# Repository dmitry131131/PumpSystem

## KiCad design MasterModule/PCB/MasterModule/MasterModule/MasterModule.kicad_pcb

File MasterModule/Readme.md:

# MasterModule

Мастер-модуль на STM32F103 для управления модулями насосов по CAN.

- [Code](Code/Readme.md) — прошивка, конфигурация платы, сборка и прошивка через ST-Link.
- `PCB/` — проект печатной платы.
- `3DModel/` — механические модели.

Сборка из каталога `MasterModule`:

```bash
cd Code
cmake --preset Debug
cmake --build --preset Debug
```

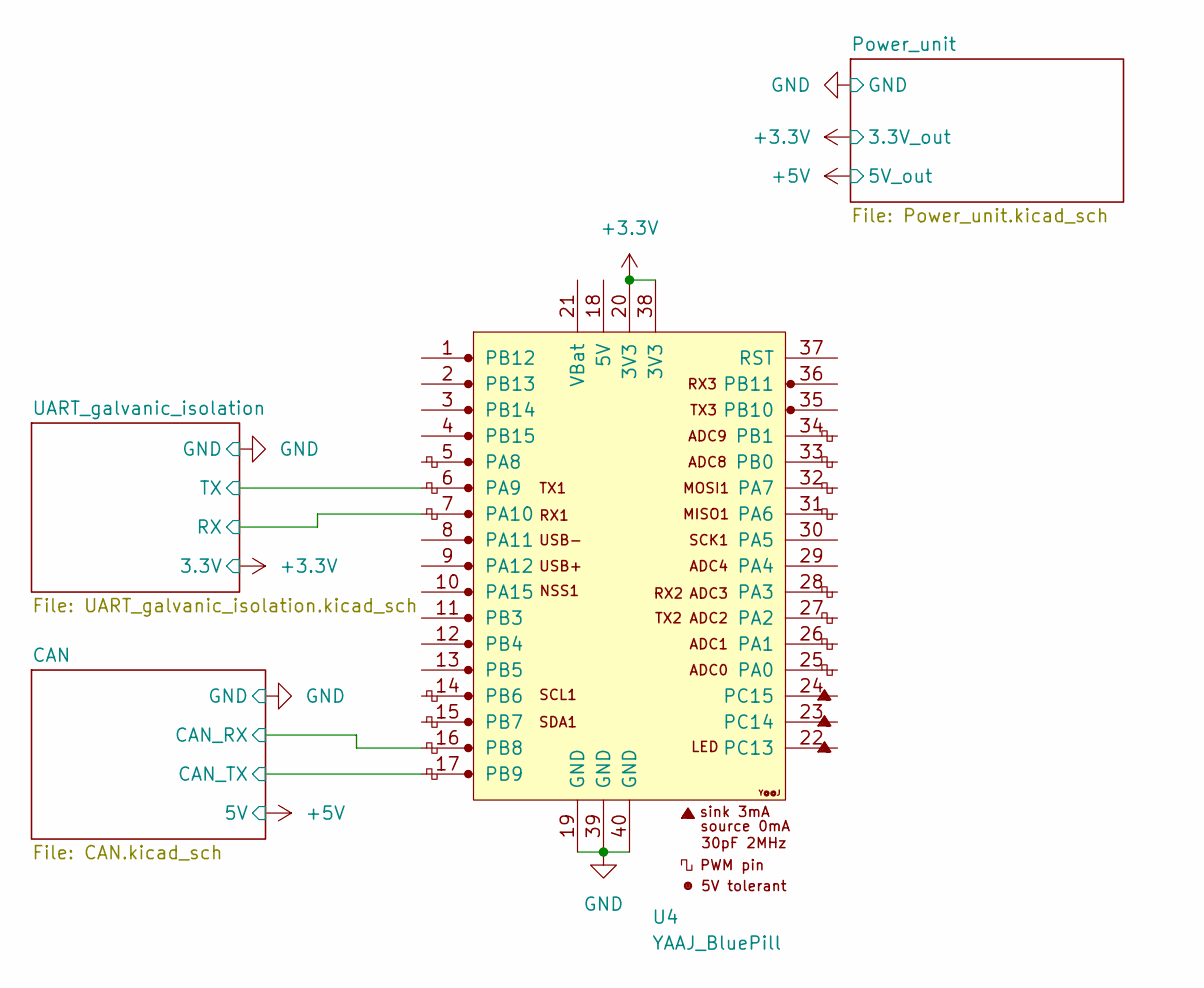
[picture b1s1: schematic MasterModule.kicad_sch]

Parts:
U4: YAAJ_BluePill; YAAJ_BluePill_1

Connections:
+3.3V: U4.20 (3V3), U4.38 (3V3); also elsewhere on the board
/CAN/CAN_RX: U4.16 (PB8); also elsewhere on the board
/CAN/CAN_TX: U4.17 (PB9); also elsewhere on the board
/UART_galvanic_isolation/RX: U4.7 (PA10); also elsewhere on the board
/UART_galvanic_isolation/TX: U4.6 (PA9); also elsewhere on the board
GND: U4.19 (GND), U4.39 (GND), U4.40 (GND); also elsewhere on the board

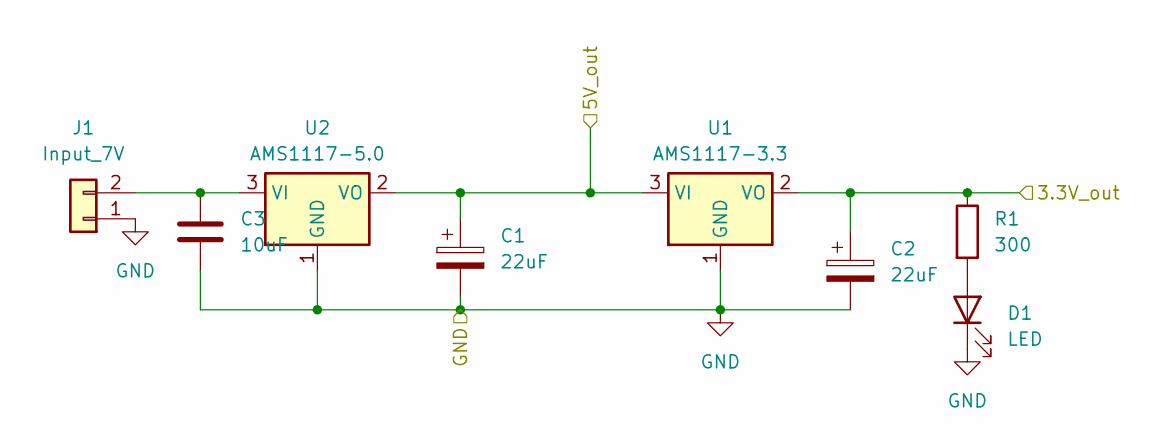
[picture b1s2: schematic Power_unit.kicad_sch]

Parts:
C1, C2: 22uF; C_1210_3225Metric_Pad1.33x2.70mm_HandSolder
C3: 10uF; C_0603_1608Metric_Pad1.08x0.95mm_HandSolder
D1: LED; LED_0805_2012Metric_Pad1.15x1.40mm_HandSolder
J1: Input_7V; TerminalBlock_Phoenix_MKDS-1,5-2-5.08_1x02_P5.08mm_Horizont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
R1: 300; R_0805_2012Metric_Pad1.20x1.40mm_HandSolder
U1: AMS1117-3.3; SOT-223-3_TabPin2
U2: AMS1117-5.0; SOT-223-3_TabPin2

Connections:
+3.3V: C2.1, R1.1, U1.2 (VO); also elsewhere on the board
+5V: C1.1, U1.3 (VI), U2.2 (VO); also elsewhere on the board
GND: C1.2, C2.2, C3.2, D1.1 (K), J1.1, U1.1 (GND), U2.1 (GND); also elsewhere on the board
unnamed: D1.2 (A), R1.2
unnamed: C3.1, J1.2, U2.3 (VI)

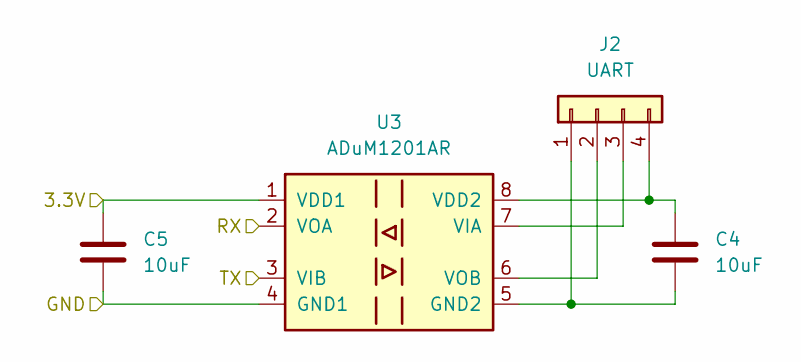
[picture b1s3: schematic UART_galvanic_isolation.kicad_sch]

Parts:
C4, C5: 10uF; C_0805_2012Metric_Pad1.18x1.45mm_HandSolder
J2: UART; JST_XH_B4B-XH-A_1x04_P2.50mm_Vertical
U3: ADuM1201AR; SOIC-8_3.9x4.9mm_P1.27mm

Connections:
+3.3V: C5.1, U3.1 (VDD1); also elsewhere on the board
/UART_galvanic_isolation/RX: U3.2 (VOA); also elsewhere on the board
/UART_galvanic_isolation/TX: U3.3 (VIB); also elsewhere on the board
GND: C5.2, U3.4 (GND1); also elsewhere on the board
unnamed: C4.2, J2.1, U3.5 (GND2)
unnamed: J2.2, U3.6 (VOB)
unnamed: J2.3, U3.7 (VIA)
unnamed: C4.1, J2.4, U3.8 (VDD2)

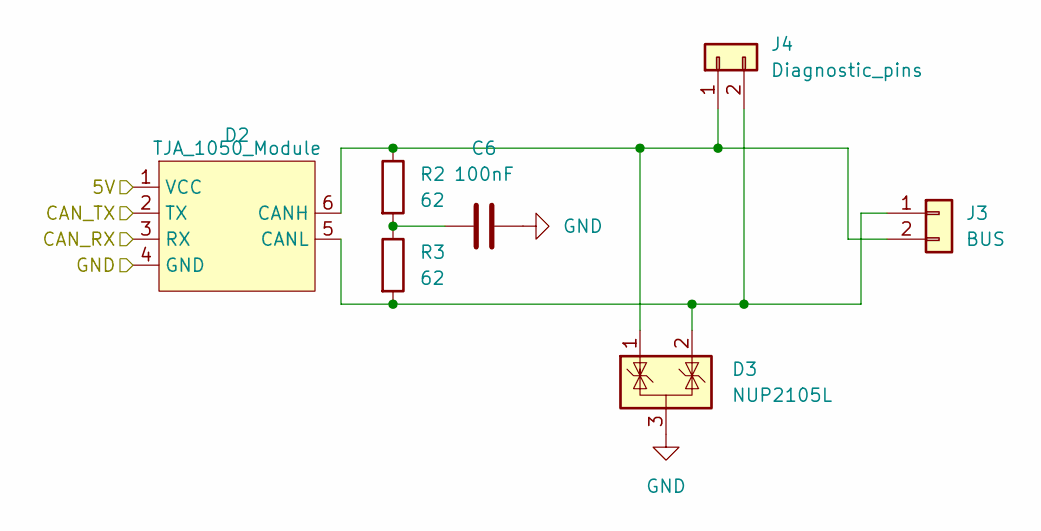
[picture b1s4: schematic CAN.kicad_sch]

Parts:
C6: 100nF; C_0805_2012Metric_Pad1.18x1.45mm_HandSolder
D2: TJA_1050_Module; TJA1050_module
D3: NUP2105L; SOT-23
J3: BUS; JST_XH_B2B-XH-A_1x02_P2.50mm_Vertical
J4: Diagnostic_pins; PinSocket_1x02_P2.54mm_Vertical
R2, R3: 62; R_0805_2012Metric_Pad1.20x1.40mm_HandSolder

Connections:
GND: C6.2, D3.3 (A); also elsewhere on the board
unnamed: C6.1, R2.2, R3.1
unnamed 14: D2.5 (CANL), D3.2 (K), J3.1, J4.2, R3.2; also elsewhere on the board
unnamed 15: D2.6 (CANH), D3.1 (K), J3.2, J4.1, R2.1; also elsewhere on the board

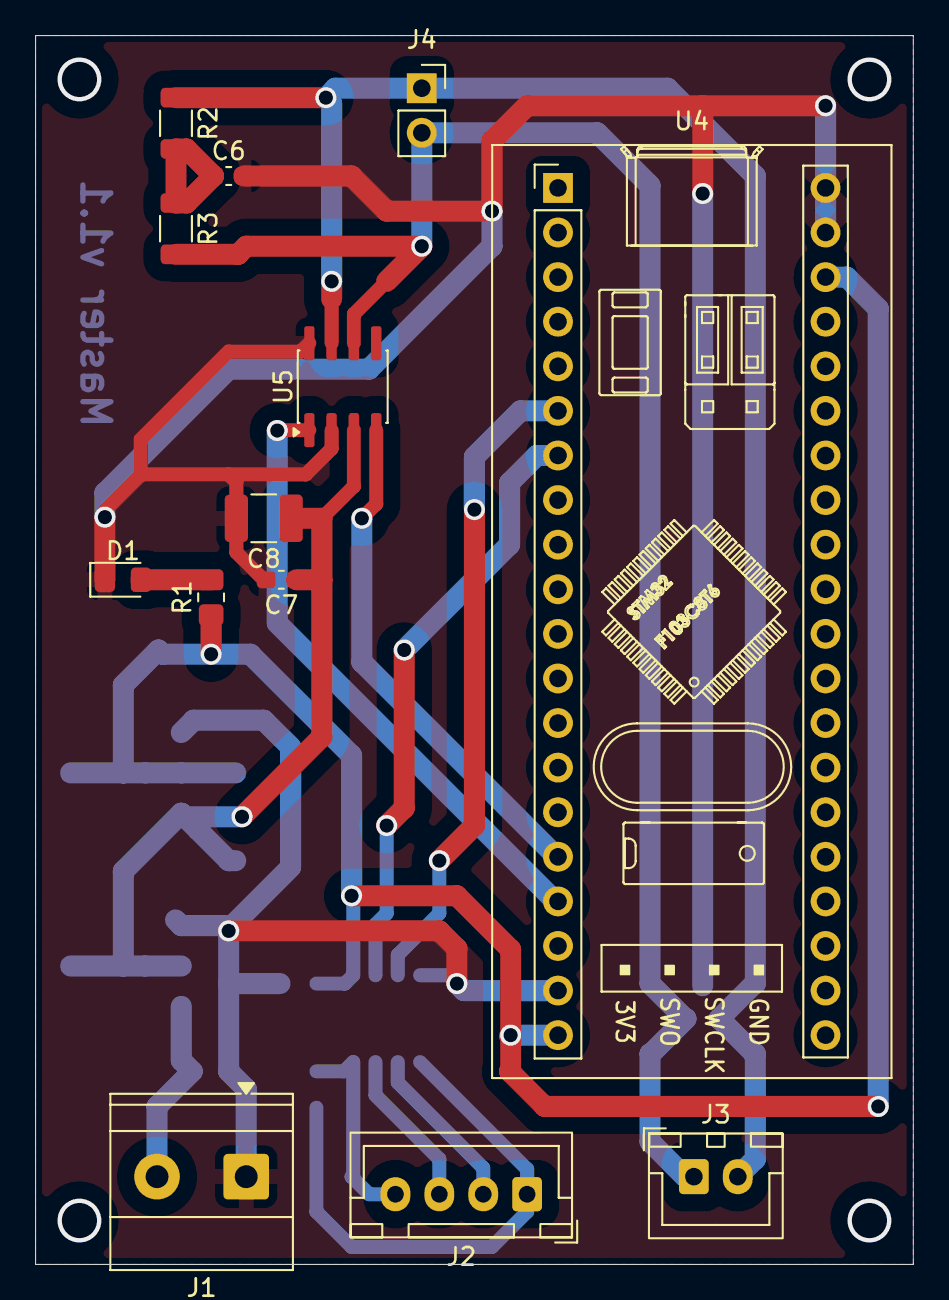
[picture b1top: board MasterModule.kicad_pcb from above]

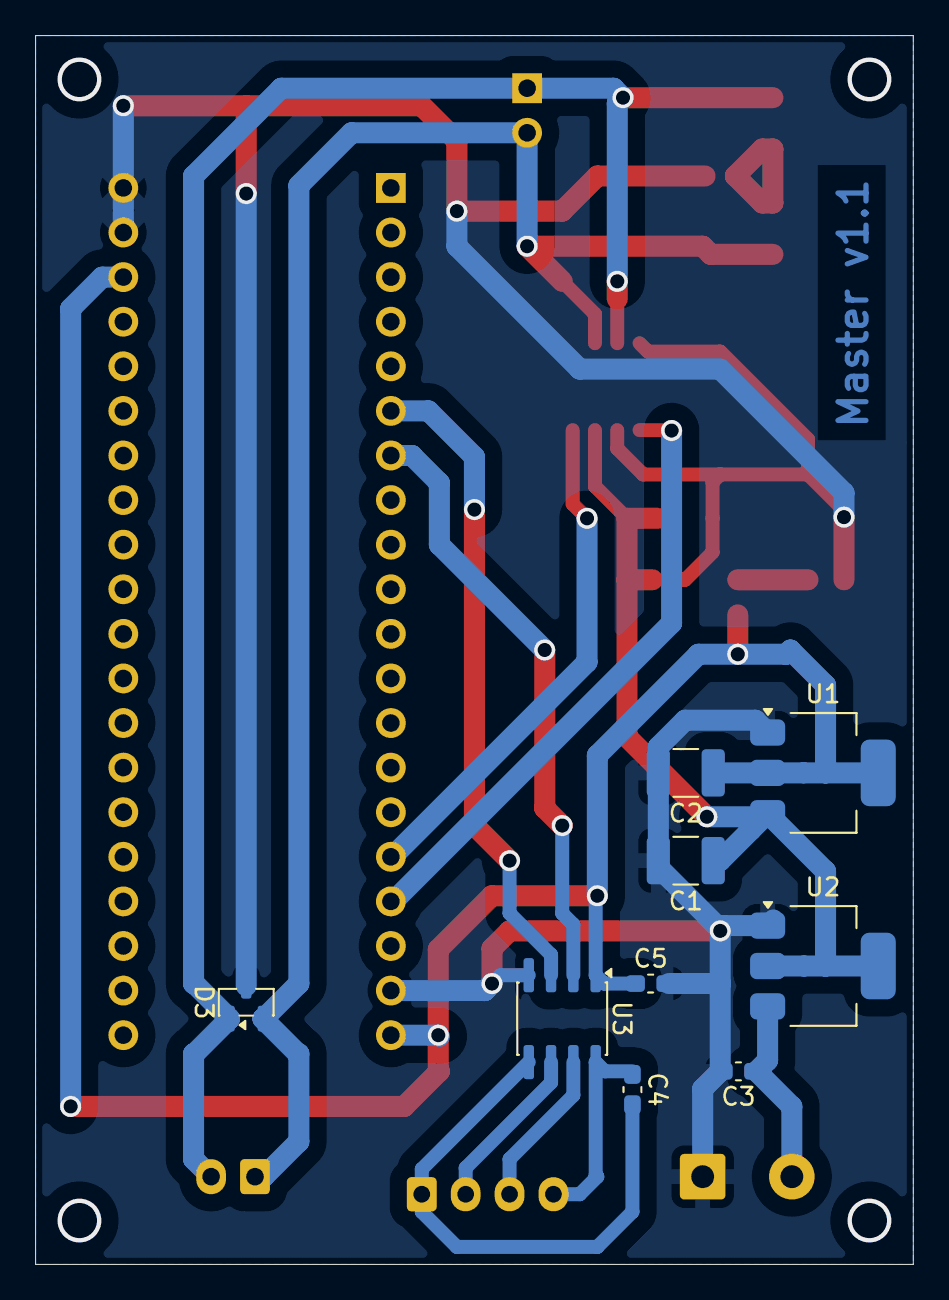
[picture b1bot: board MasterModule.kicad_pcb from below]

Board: 2 copper layers, 50.0 x 70.0 mm, 22 parts (9 on the bottom side), 16 nets.

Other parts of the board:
C7: 100nF; C_0603_1608Metric_Pad1.08x0.95mm_HandSolder
C8: 47uF; C_1210_3225Metric_Pad1.33x2.70mm_HandSolder
U5: TJA1051T; SOIC-8_3.9x4.9mm_P1.27mm

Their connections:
+5V: C7.1, C8.1, U5.3 (VCC); also elsewhere on the board
/CAN/CAN_RX: U5.4 (RXD); also elsewhere on the board
/CAN/CAN_TX: U5.1 (TXD); also elsewhere on the board
GND: C7.2, C8.2, U5.2 (GND), U5.8 (S); also elsewhere on the board
unnamed 14: U5.6 (CANL); also elsewhere on the board
unnamed 15: U5.7 (CANH); also elsewhere on the board

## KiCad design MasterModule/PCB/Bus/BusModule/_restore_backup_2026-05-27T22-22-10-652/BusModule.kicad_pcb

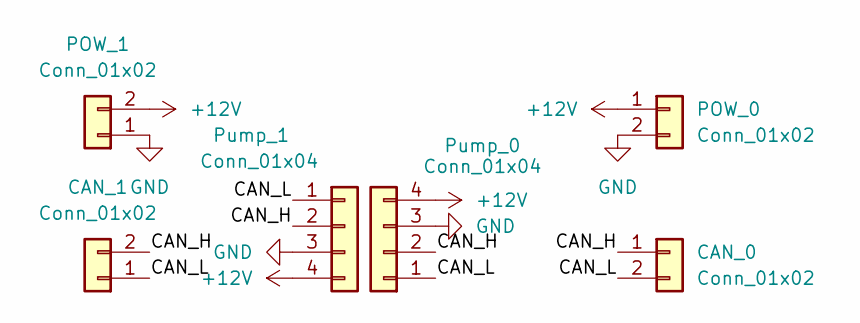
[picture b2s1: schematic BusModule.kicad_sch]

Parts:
CAN_0, CAN_1: Conn_01x02; JST_XH_B2B-XH-A_1x02_P2.50mm_Vertical
POW_0, POW_1: Conn_01x02; TerminalBlock_MaiXu_MX126-5.0-02P_1x02_P5.00mm
Pump_0, Pump_1: Conn_01x04; JST_XH_B4B-XH-A_1x04_P2.50mm_Vertical

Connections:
+12V: POW_0.1, POW_1.2, Pump_0.4, Pump_1.4
/CAN_H: CAN_0.1, CAN_1.2, Pump_0.2, Pump_1.2
/CAN_L: CAN_0.2, CAN_1.1, Pump_0.1, Pump_1.1
GND: POW_0.2, POW_1.1, Pump_0.3, Pump_1.3

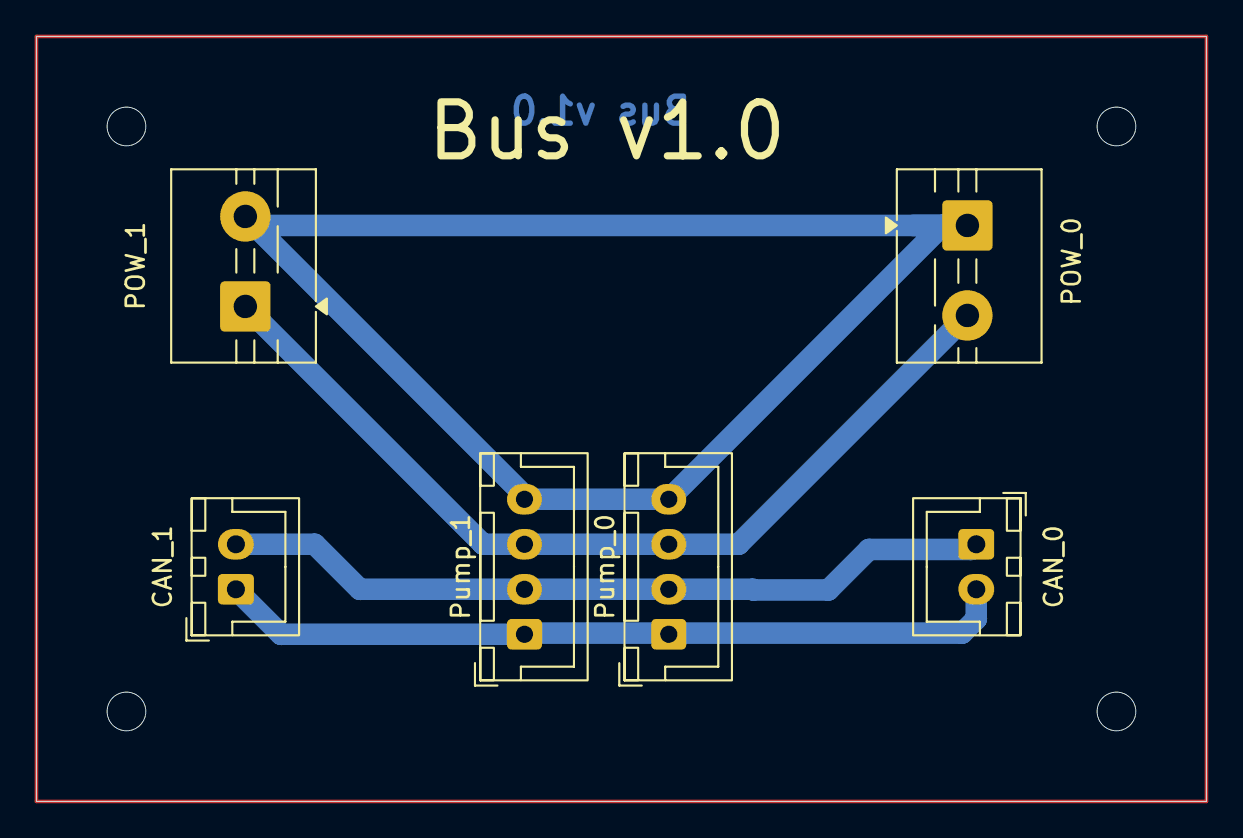
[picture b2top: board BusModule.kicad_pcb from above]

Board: 2 copper layers, 65.0 x 42.5 mm, 6 parts (0 on the bottom side), 4 nets.

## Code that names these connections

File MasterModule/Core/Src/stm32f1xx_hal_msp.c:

/* USER CODE BEGIN Header */
/**
  ******************************************************************************
  * @file         stm32f1xx_hal_msp.c
  * @brief        This file provides code for the MSP Initialization
  *               and de-Initialization codes.
  ******************************************************************************
  * @attention
  *
  * Copyright (c) 2026 STMicroelectronics.
  * All rights reserved.
  *
  * This software is licensed under terms that can be found in the LICENSE file
  * in the root directory of this software component.
  * If no LICENSE file comes with this software, it is provided AS-IS.
  *
  ******************************************************************************
  */
/* USER CODE END Header */

/* Includes ------------------------------------------------------------------*/
#include "main.h"
/* USER CODE BEGIN Includes */

/* USER CODE END Includes */

/* Private typedef -----------------------------------------------------------*/
/* USER CODE BEGIN TD */

/* USER CODE END TD */

/* Private define ------------------------------------------------------------*/
/* USER CODE BEGIN Define */

/* USER CODE END Define */

/* Private macro -------------------------------------------------------------*/
/* USER CODE BEGIN Macro */

/* USER CODE END Macro */

/* Private variables ---------------------------------------------------------*/
/* USER CODE BEGIN PV */

/* USER CODE END PV */

/* Private function prototypes -----------------------------------------------*/
/* USER CODE BEGIN PFP */

/* USER CODE END PFP */

/* External functions --------------------------------------------------------*/
/* USER CODE BEGIN ExternalFunctions */

/* USER CODE END ExternalFunctions */

/* USER CODE BEGIN 0 */

/* USER CODE END 0 */
/**
  * Initializes the Global MSP.
  */
void HAL_MspInit(void)
{

  /* USER CODE BEGIN MspInit 0 */

  /* USER CODE END MspInit 0 */

  __HAL_RCC_AFIO_CLK_ENABLE();
  __HAL_RCC_PWR_CLK_ENABLE();

  /* System interrupt init*/

  /** DISABLE: JTAG-DP Disabled and SW-DP Disabled
  */
  __HAL_AFIO_REMAP_SWJ_DISABLE();

  /* USER CODE BEGIN MspInit 1 */

  /* USER CODE END MspInit 1 */
}

/**
  * @brief CAN MSP Initialization
  * This function configures the hardware resources used in this example
  * @param hcan: CAN handle pointer
  * @retval None
  */
void HAL_CAN_MspInit(CAN_HandleTypeDef* hcan)
{
  GPIO_InitTypeDef GPIO_InitStruct = {0};
  if(hcan->Instance==CAN1)
  {
    /* USER CODE BEGIN CAN1_MspInit 0 */

    /* USER CODE END CAN1_MspInit 0 */
    /* Peripheral clock enable */
    __HAL_RCC_CAN1_CLK_ENABLE();

    __HAL_RCC_GPIOB_CLK_ENABLE();
    /**CAN GPIO Configuration
    PB8     ------> CAN_RX
    PB9     ------> CAN_TX
    */
    GPIO_InitStruct.Pin = GPIO_PIN_8;
    GPIO_InitStruct.Mode = GPIO_MODE_INPUT;
    GPIO_InitStruct.Pull = GPIO_NOPULL;
    HAL_GPIO_Init(GPIOB, &GPIO_InitStruct);

    GPIO_InitStruct.Pin = GPIO_PIN_9;
    GPIO_InitStruct.Mode = GPIO_MODE_AF_PP;
    GPIO_InitStruct.Speed = GPIO_SPEED_FREQ_HIGH;
    HAL_GPIO_Init(GPIOB, &GPIO_InitStruct);

    __HAL_AFIO_REMAP_CAN1_2();

    /* CAN1 interrupt Init */
    HAL_NVIC_SetPriority(USB_LP_CAN1_RX0_IRQn, 1, 0);
    HAL_NVIC_EnableIRQ(USB_LP_CAN1_RX0_IRQn);
    HAL_NVIC_SetPriority(CAN1_SCE_IRQn, 0, 0);
    HAL_NVIC_EnableIRQ(CAN1_SCE_IRQn);
    /* USER CODE BEGIN CAN1_MspInit 1 */

    /* USER CODE END CAN1_MspInit 1 */

  }

}

/**
  * @brief CAN MSP De-Initialization
  * This function freeze the hardware resources used in this example
  * @param hcan: CAN handle pointer
  * @retval None
  */
void HAL_CAN_MspDeInit(CAN_HandleTypeDef* hcan)
{
  if(hcan->Instance==CAN1)
  {
    /* USER CODE BEGIN CAN1_MspDeInit 0 */

    /* USER CODE END CAN1_MspDeInit 0 */
    /* Peripheral clock disable */
    __HAL_RCC_CAN1_CLK_DISABLE();

    /**CAN GPIO Configuration
    PB8     ------> CAN_RX
    PB9     ------> CAN_TX
    */
    HAL_GPIO_DeInit(GPIOB, GPIO_PIN_8|GPIO_PIN_9);

    /* CAN1 interrupt DeInit */
    HAL_NVIC_DisableIRQ(USB_LP_CAN1_RX0_IRQn);
    HAL_NVIC_DisableIRQ(CAN1_SCE_IRQn);
    /* USER CODE BEGIN CAN1_MspDeInit 1 */

    /* USER CODE END CAN1_MspDeInit 1 */
  }

}

/**
  * @brief UART MSP Initialization
  * This function configures the hardware resources used in this example
  * @param huart: UART handle pointer
  * @retval None
  */
void HAL_UART_MspInit(UART_HandleTypeDef* huart)
{
  GPIO_InitTypeDef GPIO_InitStruct = {0};
  if(huart->Instance==USART1)
  {
    /* USER CODE BEGIN USART1_MspInit 0 */

    /* USER CODE END USART1_MspInit 0 */
    /* Peripheral clock enable */
    __HAL_RCC_USART1_CLK_ENABLE();

    __HAL_RCC_GPIOA_CLK_ENABLE();
    /**USART1 GPIO Configuration
    PA9     ------> USART1_TX
    PA10     ------> USART1_RX
    */
    GPIO_InitStruct.Pin = GPIO_PIN_9;
    GPIO_InitStruct.Mode = GPIO_MODE_AF_PP;
    GPIO_InitStruct.Speed = GPIO_SPEED_FREQ_HIGH;
    HAL_GPIO_Init(GPIOA, &GPIO_InitStruct);

    GPIO_InitStruct.Pin = GPIO_PIN_10;
    GPIO_InitStruct.Mode = GPIO_MODE_INPUT;
    GPIO_InitStruct.Pull = GPIO_NOPULL;
    HAL_GPIO_Init(GPIOA, &GPIO_InitStruct);

    /* USART1 interrupt Init */
    HAL_NVIC_SetPriority(USART1_IRQn, 0, 0);
    HAL_NVIC_EnableIRQ(USART1_IRQn);
    /* USER CODE BEGIN USART1_MspInit 1 */

    /* USER CODE END USART1_MspInit 1 */

  }

}

/**
  * @brief UART MSP De-Initialization
  * This function freeze the hardware resources used in this example
  * @param huart: UART handle pointer
  * @retval None
  */
void HAL_UART_MspDeInit(UART_HandleTypeDef* huart)
{
  if(huart->Instance==USART1)
  {
    /* USER CODE BEGIN USART1_MspDeInit 0 */

    /* USER CODE END USART1_MspDeInit 0 */
    /* Peripheral clock disable */
    __HAL_RCC_USART1_CLK_DISABLE();

    /**USART1 GPIO Configuration
    PA9     ------> USART1_TX
    PA10     ------> USART1_RX
    */
    HAL_GPIO_DeInit(GPIOA, GPIO_PIN_9|GPIO_PIN_10);

    /* USART1 interrupt DeInit */
    HAL_NVIC_DisableIRQ(USART1_IRQn);
    /* USER CODE BEGIN USART1_MspDeInit 1 */

    /* USER CODE END USART1_MspDeInit 1 */
  }

}

/* USER CODE BEGIN 1 */

/* USER CODE END 1 */

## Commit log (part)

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2026-02-07 [Pump] Created basic functions for Pump module
2026-02-09 [Infra] Made full projet git repo
2026-02-17 [Infra] Made pipeline for STM32 programming
2026-02-18 [CAN] Add Doesn't work CAN structure
2026-02-18 [CAN] Silent + Loopback mode of CAN works
2026-02-18 [CAN] Loopback mode works (Logic Analyzer decodes the CAN protocol on physical bus )
2026-02-24 [PumpModule][CAN] Add all libs and simple example with connection between STM32 and Arduino
2026-02-28 [USB] Add CubeMX USB configuration to project
2026-03-02 [PumpModule][3DModel] Create stable mechanic part of PumpModule
2026-03-02 [PumpModule][3DModel] Add all mecanical part of PumpModule
2026-03-02 [PumpModule][3DModel] Fix Carriage for new fastener
2026-03-02 [PumpModule][Core] Add some rotation functions
2026-03-02 [PumpModule][PCB] Create Board for PumpModule electronic
2026-03-03 [PumpModule][Core] write registration code for PumpModule
2026-03-04 [PumpModule][CAN] Add registration code for PumpModule
2026-03-04 [MasterModule][Infra] Add compile_commands
2026-03-04 [MasterModule][CAN] Add code for MasterModule to make Pump registration process possible
2026-03-04 [MasterModule][CAN] Add code for responding for Registration message
2026-03-06 [MasterModule][CAN] Add Message types and Pump Registration protocol
2026-03-08 [CAN] Add stable commands and data transmission between PumpModules and Master
2026-03-10 [CAN] Realized full CAN messaged in Pump
2026-03-17 [UART] Add monitor program basic structure and add Uart protocol functions
2026-03-20 [UART] Add UART runtime to MasterModule. Refactor UART_message ctor in Monitor
2026-03-22 [UART] Made working system with monitor, master and pump
2026-04-01 [Monitor] Add whole system working (with huge bugs) showed to customer
2026-04-08 [MasterModule][PCB] Create PCB for Bus part of Master module
2026-04-23 [MasterModule][PCB] Add full traced BUS circuit board
2026-04-29 [BUS][PCB] Fix chipboard size
2026-05-18 Actual master module CAD
2026-05-24 [BUS][PCB] Made PCB template for manufacturing
2026-05-28 [PCB][Bus] Add GND and 12V poligon (Bus v1.1)
2026-06-05 [BUS] Add coper fields
2026-06-09 [PCB] Made Pump v1.0 PCB
2026-06-09 [PCB][Pump Module] Fixed PCB pinout
2026-06-09 [PCB][PumpModule] Fixed input power pinout. Changed indication pin and add status LED to A0 pin
2026-06-09 [PCB][BUS] Fix power connections plates (v 1.2)
2026-06-11 [PCB][MasterModule] Add PCB width and height and add basic elements
2026-06-13 [PCB][PumpModule] Add manufacturing files
2026-06-14 [PCB][MasterModule] Create MasterModule v.1.0
2026-06-15 [PCB][MasterModule] Manufactured master module v1.0
2026-06-17 [PCB][MasterModule] Fix CAN transmitter to TJA1050 chip (Master v1.1)
